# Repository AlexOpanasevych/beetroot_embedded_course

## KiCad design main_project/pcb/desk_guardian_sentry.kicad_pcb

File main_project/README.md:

# Main Project — Desk Guardian: Networked Sentry

A capstone that extends the **miniproject_module5** "Desk Guardian" PIR/buzzer/LED
board into a small networked environmental sentry: it still barks at motion, but
now also reads temperature/humidity/pressure, spins a PID-controlled cooling fan,
and serves a live status dashboard over Wi-Fi — no PC/serial monitor required to
see what it's doing.

Hardware is **Desk Guardian PCB rev B** (`pcb/`): the miniproject_module5 board
with the PIR/buzzer/LED circuitry unchanged, plus an on-board BME280 header and
a fan low-side driver for the new features — see [PCB — rev B](#pcb--rev-b).

## What it reuses, and from where

| Piece | Reused from | What changed |
|---|---|---|
| I2C driver style (`driver/i2c_master.h`) | module4.2 (SSD1306 ticker) | Same bus-init pattern, new device (BME280) instead of an OLED |
| BME280 register map + Bosch compensation math | module4.4 (STM32 BME280 telemetry) | Ported from STM32 HAL calls to ESP-IDF's `i2c_master_transmit`/`_transmit_receive` |
| Multi-producer -> single-consumer FreeRTOS queue | module6.3 | Two producers (BME280 poll task, PIR task) instead of three; one aggregator task owns all shared state |
| ISR + binary semaphore, 0% CPU while idle | module6.5 (emergency-stop task) | Applied to the PIR input instead of a panic button |
| PID fan controller (incl. the D-sign fix, anti-windup, and min-duty output normalization) | module5.6 | Same math, fed by BME280 temperature instead of a thermistor divider; PID step runs whenever a fresh reading arrives instead of on a fixed 50 ms timer |
| Wi-Fi STA connect (event group, auto-reconnect) | miniproject_module3 (Wi-Fi subwoofer amp) | Same connect logic, serving a status page instead of streaming audio |
| Buzzer/LED "bark" cadence | module1.3 (flash/gap blink constants) | Same 80 ms/60 ms flash/gap timing, applied to the buzzer+LED alert instead of a plain blink |
| PIR + buzzer + LED-eyes hardware | miniproject_module5 (Desk Guardian PCB) | Unchanged — same pins, same RC filtering |
| Fan driver circuit (Q2/D2/R11) | miniproject_module5's buzzer driver (Q1/D1/R6) | Same MMBT3904 + 1N4148 topology, switched to +5V, plus a base pull-down and bulk cap |

## Wiring

Carried over unchanged from miniproject_module5:

| Signal | ESP32-S3 pin | Notes |
|---|---|---|
| PIR_IN | IO4 | RC-filtered on the board, R5 already pulls it down when idle |
| Buzzer control | IO5 | via the board's existing NPN transistor driver |
| LED eye 1 | IO6 | |
| LED eye 2 | IO7 | |

New on rev B (were no-connect pins on rev A):

| Signal | ESP32-S3 pin | On-board | Notes |
|---|---|---|---|
| BME280 SDA | IO8 (U2 pad 12) | J3 pin 4, R9 4.7k pull-up, TP1 | |
| BME280 SCL | IO9 (U2 pad 17) | J3 pin 3, R10 4.7k pull-up, TP2 | |
| BME280 VIN / GND | 3V3 / GND | J3 pins 1 / 2, C6 100nF | GY-BME280 pin order (VIN GND SCL SDA); module's SDO tied to GND -> address 0x76 |
| Fan PWM | IO18 (U2 pad 11) | R11 1k -> Q2 base, TP3 | R12 10k holds the fan off while IO18 floats during boot |
| Fan | +5V / FAN_DRV | J4 pins 1 / 2, D2 flyback, C7 10uF, TP4 | 5V fan, **<= 150 mA** (MMBT3904 is rated 200 mA) |

## Architecture

```
                 ISR (rising edge)
   PIR (IO4) ────────────────────► motion semaphore ──► pir_task
                                                            │
                                                     bark (buzzer+LEDs,
                                                      module1.3 cadence)
                                                            │
                                                            ▼
   BME280 (I2C) ──► bme280_task ──────────────────►  sensor_hub queue
      (every 2s)                                    (module6.3 pattern)
                                                            │
                                                            ▼
                                                    aggregator_task
                                                  (single consumer,
                                                 owns system_state_t)
                                                     │           │
                                          fan_pid_on_new_        │
                                          temperature()          │
                                                     │           │
                                                     ▼           ▼
                                              LEDC fan PWM   sensor_hub_get_state()
                                               (IO18)              │
                                                                   ▼
                                                          web_dashboard (/, /status.json)
                                                             served over Wi-Fi STA
```

`aggregator_task` is the *only* reader of the shared queue and the only writer
of the sensor/motion fields of `system_state_t` — exactly the module6.3
invariant ("no shared mutable state between producers; the queue itself is the
synchronization"). The few status fields that don't come from sensors (fan
duty, Wi-Fi state, CPU load) are written by their owners through
`sensor_hub_set_*()`, under the same mutex. `pir_task` reacts to motion
immediately and independently of the queue (the buzzer/LEDs can't wait on a
consumer task), then reports the event into the same queue afterwards so the
dashboard picks it up too.

A fourth task, `cpu_monitor_task` (every 3s), measures CPU load and
critical-section timing — see the Performance sections below.

## Reliability

`aggregator_task`, `pir_task`, `bme280_task`, and `cpu_monitor_task` are each
registered with ESP-IDF's task watchdog (`esp_task_wdt_add`) and reset it
(`esp_task_wdt_reset`) at least every ~3s — including on `pir_task`'s idle
poll and inside its post-motion cooldown (which is a menuconfig value and,
together with the bark, already exceeds 5s at the default, so it sleeps in 1s
slices). A task that truly hangs (stuck I2C transaction, deadlocked mutex,
etc.) trips the 5s watchdog and reboots the board (`CONFIG_ESP_TASK_WDT_PANIC=y`)
instead of silently freezing the sentry, while legitimate quiet periods never
trip it.

## Performance — CPU load monitoring

`cpu_monitor.cpp` samples FreeRTOS run-time stats every 3s
(`configGENERATE_RUN_TIME_STATS`, `ulTaskGetIdleRunTimeCounter()`) and
computes load as a rolling window (delta between samples), not a
since-boot average, so it reflects current conditions rather than slowly
drifting as uptime grows. Logged every sample (`ESP_LOGW` once load reaches
the 70% budget, `ESP_LOGI` otherwise) and pushed to the dashboard's
`cpu_load_pct` field. Not yet measured on hardware; the busiest paths should
be the 2s BME280/PID cycle, dashboard requests, and Wi-Fi, so load is expected
to stay far below the 70% budget — the log will confirm or refute that.

## Performance — critical-section timing

`crit_timing.h/.cpp` is a small min/max/avg microsecond recorder
(`esp_timer_get_time()`-based) used to actually measure, not just assume,
how long this project's two real critical sections stay held:

- **`sensor_hub`'s state mutex** — every `sensor_hub_get_state()` /
  `_set_fan_duty()` / `_set_wifi()` / `_set_cpu_load()` call and
  `aggregator_task`'s own update time the span between a successful
  `xSemaphoreTake` and the matching `xSemaphoreGive` (wait-to-acquire time
  is deliberately excluded — that's contention, not hold time).
- **The PIR GPIO ISR** (`pir_isr_handler`) — timed end-to-end, since the
  whole handler body is the "critical section" there. `crit_timing_record()`
  is `IRAM_ATTR` (pure integer math) so it's safe to call from an ISR that's
  itself `IRAM_ATTR`.

The stats themselves are shared data too, so they're guarded: the mutex
stats are only touched while holding the state mutex, and the ISR stats sit
behind a `portMUX` spinlock shared by the ISR and the reporting task.

Both get logged (and their stats reset) every 3s alongside the CPU load
report, by `cpu_monitor.cpp`. Expect low-single-digit microseconds for the
mutex (it only ever guards a small struct copy/field write) and a similar
order of magnitude for the ISR (it just gives a semaphore) — if either
climbs into the hundreds of microseconds or higher, that's a real regression
worth investigating, not noise.

## PCB — rev B

KiCad 10 project in `pcb/desk_guardian_sentry.*`, derived from
miniproject_module5's `desk_guardian` board (the original there is left
untouched as the rev A submission).

- **Board:** 2-layer, 78 x 106 mm, ESP32-S3-WROOM-1 soldered directly
  (antenna overhanging the top edge), USB-C 5V in -> AMS1117-3.3 LDO.
- **Rev B additions** (lower-right area, previously empty): J3 BME280 header,
  R9/R10 I2C pull-ups, C6 decoupling; Q2/D2/R11/R12/C7 fan driver, J4 fan
  header; test points TP1 SDA, TP2 SCL, TP3 FAN_PWM, TP4 FAN_DRV, TP5 GND.
  Both headers sit on the right board edge for off-board cabling.
- **Power / filtering:** C6 100nF right at the BME280 header's 3V3/GND pins;
  C7 10uF bulk on +5V next to the fan header, to absorb motor current spikes
  locally instead of pulling them back through the whole +5V run. D2 clamps
  the fan's inductive kick when Q2 switches off.
- **Signal / power separation:** F.Cu is a solid GND pour, so the new routing
  stays on B.Cu wherever possible — 310 of 367 mm (84%); the F.Cu pieces are
  short pad escapes plus the 15 mm local FAN_BASE net between R11/R12/Q2.
  Power runs are wider (+5V / FAN_DRV 0.6 mm, +3V3 0.4 mm) than signals
  (0.25 mm). Fan current reaches J4 on its own 0.6 mm +5V branch from the
  USB input rather than through the LDO's traces (~11 mV drop at 150 mA).
- **High-speed considerations:** nothing on this board is fast — I2C runs at
  100 kHz and the fan PWM at 5 kHz, so trace length and impedance matching
  aren't critical. The one RF-sensitive part, the WROOM antenna, has no
  copper routed under or near it.
- **Verification:** ERC 0 errors; DRC 0 errors, 0 unconnected items, 0
  schematic-parity issues. The only warnings are ones rev A already had
  (library-version drift on a few symbols, U2's silkscreen clipped by the
  board edge because the antenna overhangs).

## Build & run

```
pio run -t menuconfig
# -> "Desk Guardian Sentry Configuration": set your Wi-Fi SSID/password,
#    the fan's PID setpoint temperature, and the motion cooldown.

pio run -e esp32-s3-devkitc-1
pio run -e esp32-s3-devkitc-1 -t upload
pio device monitor -b 115200   # watch for "Got IP: ..."
```

Then open `http://<that-ip>/` in a browser on the same LAN. The page polls
`/status.json` every 2 seconds; a motion event turns the "Motion" card red
until the next PIR cooldown window ends.

## Known limitations

- Wi-Fi is STA-only with no fallback: `wifi_sta_init()` waits up to 15s for
  the initial connection, then boots the rest of the system (PIR sentry,
  fan PID) regardless — the dashboard just stays unreachable until a
  connection succeeds in the background (watch the serial log for
  "No Wi-Fi after..." vs. "Got IP: ...").
- No wall-clock timestamps: `last_motion_ms`/`bme280_updated_ms` are
  milliseconds since boot (`xTaskGetTickCount()`), not real time — the board
  has no RTC and this project doesn't add SNTP, so treat them as relative
  ("Xs ago"), not absolute.
- The dashboard has no auth — anyone on the LAN can view it (and see when
  you're not at your desk). Fine for a demo, not for anything beyond a
  trusted home/lab network, same caveat as the subwoofer amp's UDP stream.
- PID coefficients are the module5.6 starting values, carried over as-is;
  the BME280's thermal mass/response in open air will differ from the
  thermistor-on-a-divider setup they were tuned for, so expect to retune
  Kp/Ki/Kd (watch the `SP/PV/OUT/PWM` log lines) once real hardware is wired up.

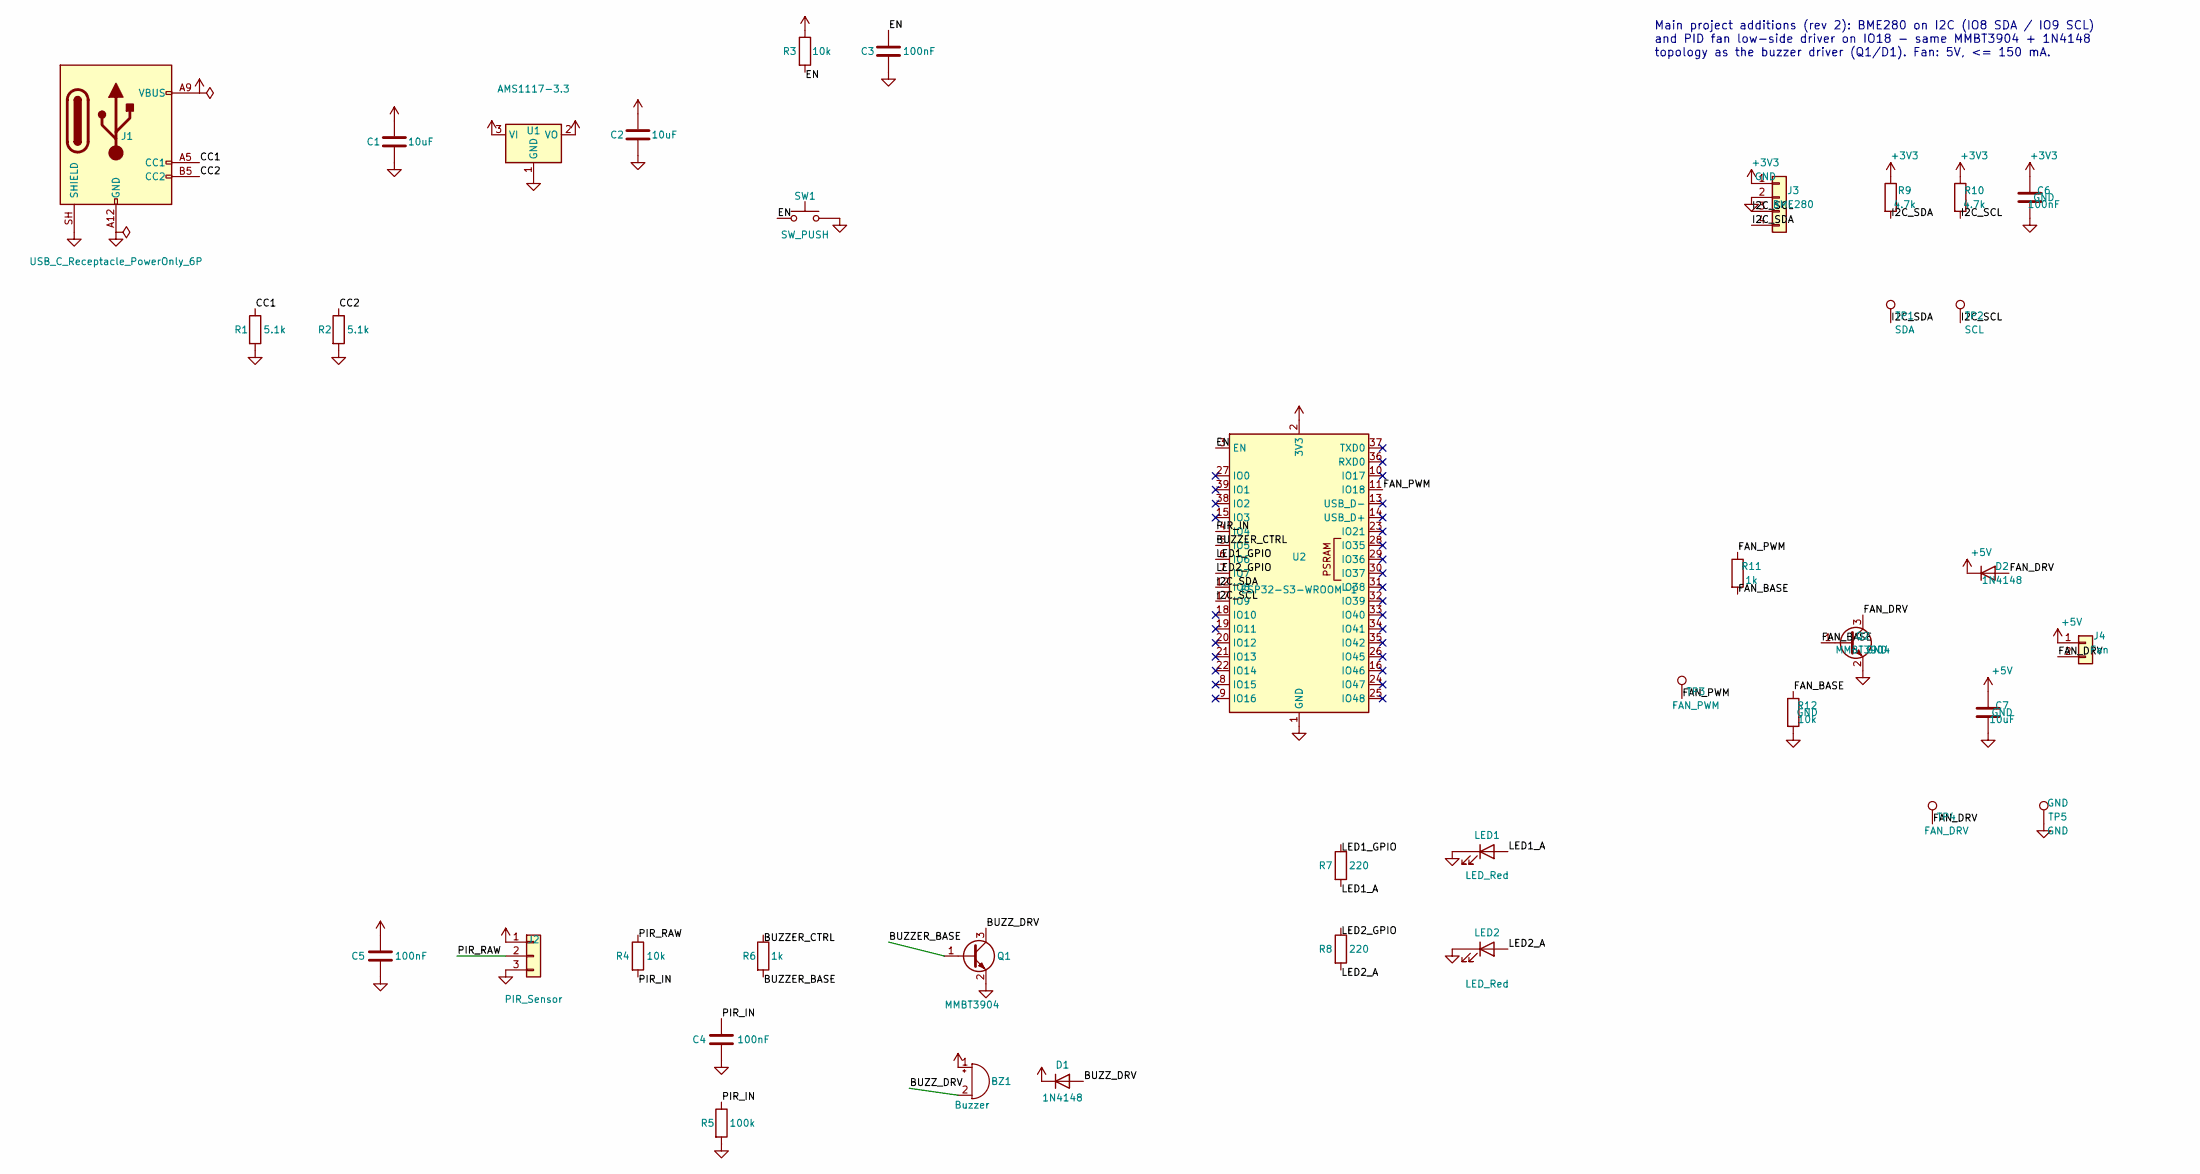
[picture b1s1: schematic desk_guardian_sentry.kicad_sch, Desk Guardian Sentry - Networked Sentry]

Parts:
BZ1: Buzzer; Buzzer_12x9.5RM7.6
C1, C2, C7: 10uF; C_0805_2012Metric
C3, C4, C5, C6: 100nF; C_0603_1608Metric
D1, D2: 1N4148; D_SOD-123
J1: USB_C_Receptacle_PowerOnly_6P; USB_C_Receptacle_GCT_USB4125-xx-x_6P_TopMnt_Horizontal
J2: PIR_Sensor; PinHeader_1x03_P2.54mm_Vertical
J3: BME280; PinHeader_1x04_P2.54mm_Vertical
J4: Fan; PinHeader_1x02_P2.54mm_Vertical
LED1, LED2: LED_Red; LED_0603_1608Metric
Q1, Q2: MMBT3904; SOT-23
R1, R2: 5.1k; R_0603_1608Metric
R3, R4, R12: 10k; R_0603_1608Metric
R5: 100k; R_0603_1608Metric
R6, R11: 1k; R_0603_1608Metric
R7, R8: 220; R_0603_1608Metric
R9, R10: 4.7k; R_0603_1608Metric
SW1: SW_PUSH; SW_SPST_B3U-1000P
TP1: SDA; TestPoint_Pad_D1.5mm
TP2: SCL; TestPoint_Pad_D1.5mm
TP3: FAN_PWM; TestPoint_Pad_D1.5mm
TP4: FAN_DRV; TestPoint_Pad_D1.5mm
TP5: GND; TestPoint_Pad_D1.5mm
U1: AMS1117-3.3; SOT-223-3_TabPin2
U2: ESP32-S3-WROOM-1

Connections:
+3V3: BZ1.1 (+), C2.1, C5.1, C6.1, D1.1 (K), J2.1, J3.1, R3.1, R9.1, R10.1, U1.2 (VO), U2.2 (3V3)
+5V: C1.1, C7.1, D2.1 (K), J1.A9 (VBUS), J1.B9 (VBUS), J4.1, U1.3 (VI)
/BUZZER_BASE: Q1.1 (B), R6.2
/BUZZER_CTRL: R6.1, U2.5 (IO5)
/BUZZ_DRV: BZ1.2 (-), D1.2 (A), Q1.3 (C)
/CC1: J1.A5 (CC1), R1.1
/CC2: J1.B5 (CC2), R2.1
/EN: C3.1, R3.2, SW1.1, U2.3 (EN)
/FAN_BASE: Q2.1 (B), R11.2, R12.1
/FAN_DRV: D2.2 (A), J4.2, Q2.3 (C), TP4.1
/FAN_PWM: R11.1, TP3.1, U2.11 (IO18)
/I2C_SCL: J3.3, R10.2, TP2.1, U2.17 (IO9)
/I2C_SDA: J3.4, R9.2, TP1.1, U2.12 (IO8)
/LED1_A: LED1.2 (A), R7.2
/LED1_GPIO: R7.1, U2.6 (IO6)
/LED2_A: LED2.2 (A), R8.2
/LED2_GPIO: R8.1, U2.7 (IO7)
/PIR_IN: C4.1, R4.2, R5.1, U2.4 (IO4)
/PIR_RAW: J2.2, R4.1
GND: C1.2, C2.2, C3.2, C4.2, C5.2, C6.2, C7.2, J1.A12 (GND), J1.B12 (GND), J1.SH (SHIELD), J2.3, J3.2, LED1.1 (K), LED2.1 (K), Q1.2 (E), Q2.2 (E), R1.2, R2.2, R5.2, R12.2, SW1.2, TP5.1, U1.1 (GND), U2.1 (GND), U2.40 (GND), U2.41 (GND)

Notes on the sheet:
Main project additions (rev 2): BME280 on I2C (IO8 SDA / IO9 SCL) and PID fan low-side driver on IO18 - same MMBT3904 + 1N4148 topology as the buzzer driver (Q1/D1). Fan: 5V, <= 150 mA.

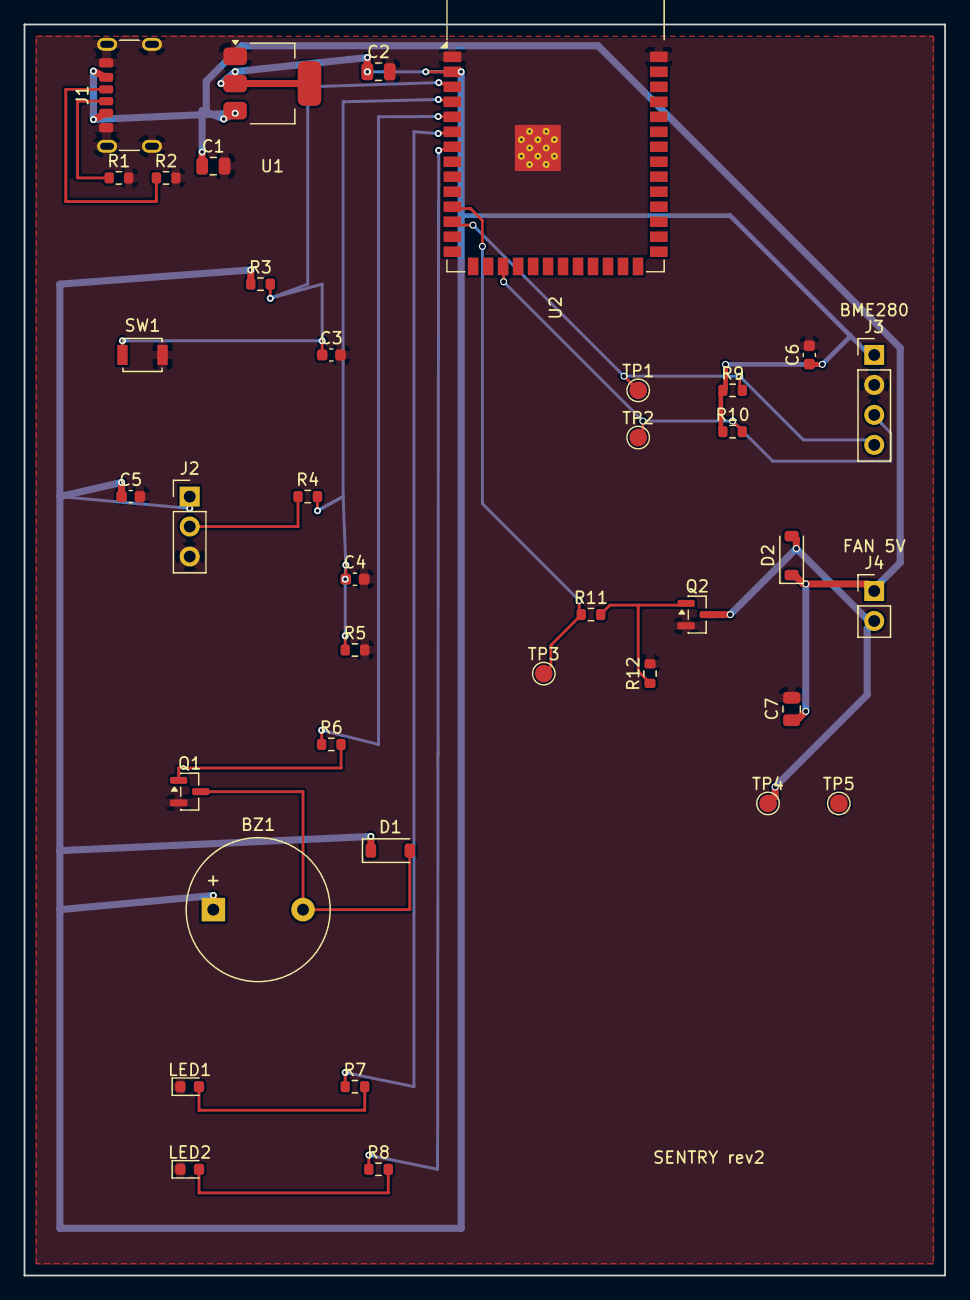
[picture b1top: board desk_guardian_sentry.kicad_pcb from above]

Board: 2 copper layers, 78.0 x 106.0 mm, 38 parts (0 on the bottom side), 20 nets.

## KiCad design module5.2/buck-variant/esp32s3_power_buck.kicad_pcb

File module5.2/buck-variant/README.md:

# Module 5.2 - ESP32-S3 Power Supply PCB Layout (Buck Converter Variant)

KiCad 10 project: the schematic from Module 5.1 (`buck-variant`), routed into a
2-layer PCB. This folder is a self-contained copy of the Module 5.1 project
(schematic + project files) plus the new, fully routed board
(`esp32s3_power_buck.kicad_pcb`), so it opens as one normal KiCad project.

The board was built programmatically with KiCad's bundled Python/`pcbnew`
(placing real library footprints, creating nets/tracks/vias from the
schematic's netlist, and adding the board outline), rather than by hand in
the PCB editor - this made it easy to derive exact pad coordinates from the
real footprint geometry and to verify placement/clearance numerically before
each DRC pass.

## Netlist source of truth

The board reproduces the schematic's netlist exactly (verified with
`--schematic-parity`, see DRC report below):

| Net | Pads |
|---|---|
| `/VIN` | J1.1, C1.1, U1.1 (VIN) |
| `/SW_NODE` | U1.2 (OUT), D1.1 (K), L1.1 |
| `+3V3` | L1.2, C2.1, U1.4 (FB), R1.2, U2.2 (3V3) |
| `/EN` | R1.1, C3.2, SW1.1, U2.3 (EN) |
| `GND` | C1.2, C2.2, C3.1, D1.2 (A), J1.2, SW1.2, U1.3 (GND+tab), U1.5 (ON/OFF), U2.1, U2.40, U2.41 |

Footprints used are exactly the ones assigned in the Module 5.1 schematic
(real KiCad library parts, no substitutions):

| Ref | Part | Footprint |
|---|---|---|
| J1 | Barrel jack | `Connector_BarrelJack:BarrelJack_CUI_PJ-063AH_Horizontal` |
| U1 | LM2596S-3.3 | `Package_TO_SOT_SMD:TO-263-5_TabPin3` |
| D1 | SS34 | `Diode_SMD:D_SMA` |
| L1 | 33uH inductor | `Inductor_SMD:L_10.4x10.4_H4.8` |
| C1 | 100uF/25V | `Capacitor_THT:CP_Radial_D6.3mm_P2.50mm` |
| C2 | 220uF/16V | `Capacitor_THT:CP_Radial_D6.3mm_P2.50mm` |
| C3 | 100nF | `Capacitor_SMD:C_0805_2012Metric` |
| R1 | 10k | `Resistor_SMD:R_0805_2012Metric` |
| SW1 | Push button | `Button_Switch_THT:SW_PUSH_6mm` |
| U2 | ESP32-S3-WROOM-1 | `RF_Module:ESP32-S3-WROOM-1` |

## Board outline

A rectangular `Edge.Cuts` outline, 90 mm x 80 mm, origin at (0,0). Size was
picked after placement: it gives the ESP32-S3 module's antenna keep-out zone
a clear margin to the board edge, keeps the buck-converter cluster's TO-263
tab and barrel jack clear of the board edge with a few mm to spare, and
leaves comfortable room for the reset network without needing to crowd
anything. It's larger than the absolute minimum a professional layout would
use, but that headroom is what made it possible to route entirely by hand
(via a script) without fighting for millimeters.

## Placement rationale

**ESP32-S3-WROOM-1 (U2)** is rotated so its antenna keep-out area (the wide
skirt at one end of the module's `F.CrtYd` courtyard - a rectangle roughly
21 mm x 48 mm, clearly larger than the module body itself) faces the board's
west edge, with the rest of the board's circuitry to the east and south of
the module body. This keeps the antenna area open (no other footprints'
courtyards or copper anywhere near it) and moves the noisy switching
regulator to the opposite side of the board from the RF module, which is
good practice for both antenna performance and switching noise coupling into
the 2.4 GHz front end.

**Buck converter switching loop (U1, D1, L1, C1, C2)** is clustered in the
board's north-east corner, physically as close together as the parts' real
footprint envelopes allow:
- `C1` (input bulk cap) sits right at U1's VIN pin.
- `D1` (catch diode) and `L1` (inductor) sit right at U1's OUT/switch-node
  pin - this is the loop that matters most for a buck converter (VIN through
  the FET, out through L1, with D1 providing the return path when the switch
  is off), so U1-D1-L1 form a tight triangle a few mm on a side rather than
  being spread across the board.
- `C2` (output bulk cap) sits just past L1's output pin.

The real footprint sizes (the TO-263 tab, the 10.4x10.4 mm shielded
inductor, the SMA diode) set a practical lower bound on how tight this loop
can be; given those envelopes, the loop here is about as small as it can be
made without overlapping courtyards.

**Reset network (R1, C3, SW1)** sits just south of the ESP32 module's EN/3V3/
GND pin row, i.e. as close as possible to the pins it serves. `SW1` (the
physical reset button) is placed toward the south-east of that group, away
from other components, so it stays reachable if the board is mounted for
production access to the button.

**Barrel jack (J1)** is mounted on the board's south edge (rotated 180 deg so
its plug-facing side lines up with the board edge), the standard placement
for a panel/edge-mount power connector so the DC plug is accessible from
outside an enclosure.

## Trace widths

- **Power/switching nets** (`/VIN`, `/SW_NODE`, `+3V3`, `GND`): **0.8 mm**.
  These carry the LM2596's several-amp switching current (and its return
  path on GND), so a wider trace than signal-level routing is used to keep
  resistive drop and heating low, per the requirement to use ~0.6-1.0 mm for
  power nets on a buck converter board.
- **`/EN`** (reset/enable logic signal): **0.3 mm**. This is a low-current
  logic-level net (10k pull-up, 100nF cap, push button), so a standard thin
  signal trace is appropriate; no need for the extra copper power traces use.
- **Vias**: 0.8 mm pad / 0.4 mm drill (standard-size vias), used to move GND
  (and two short `/VIN` hops, see below) between layers.

## Layer stackup / GND routing strategy

Standard 2-layer board (F.Cu / B.Cu). `/VIN`, `/SW_NODE`, `+3V3` and `/EN`
are routed entirely on the top layer (F.Cu). **GND is routed as a dedicated
tree entirely on the bottom layer (B.Cu)**, reached from each SMD GND pad by
a short top-layer stub into a via, and connected directly (no via needed) at
every through-hole GND pad (C1, C2, SW1, J1 are all THT, so their GND pads
already have copper on both layers).

This was a deliberate choice over a full copper pour/zone: with only 10
parts and 5 nets, a manually-routed GND tree is simple to verify net-by-net,
and putting GND on its own layer means the four F.Cu nets can be routed
without having to dodge a GND pour, and automatically can't short into each
other's layer. It also sidesteps any question of copper near the ESP32
module's antenna keep-out area - the GND tree on B.Cu was routed clear of
that whole rectangle, and no zone/pour was added there either. A full GND
copper pour (the "nice-to-have" in the brief) was consciously skipped in
favor of finishing a clean, fully-verified manual route; the existing B.Cu
GND tree could be turned into a pour later by just adding a `B.Cu` zone over
the board outline (minus the antenna keep-out) with the existing tracks left
in place as reinforcement.

Two short `/VIN` segments (about 2 mm each, near x=52.5, y=48-50) are
deliberately routed on B.Cu via a via-hop, purely to cross under the `+3V3`
trunk trace on F.Cu at one unavoidable intersection between the ESP32
module's south side and the buck cluster - everywhere else `/VIN` stays on
F.Cu.

## Deviations / notes on the clean DRC result

- **Minimum hole size relaxed to 0.2 mm.** The official KiCad
  `RF_Module:ESP32-S3-WROOM-1` footprint defines a cluster of small
  0.2 mm-drill plated pads under pin 41 (the antenna/thermal ground contact
  area) as part of its vendor-defined land pattern - this is baked into the
  real, verified footprint, not a routing choice made here. The board's
  minimum-hole design rule was lowered from KiCad's 0.3 mm default to 0.2 mm
  so DRC checks the real footprint instead of flagging it as an error. If
  this exact module/footprint is sent to fab, confirm the chosen
  manufacturer supports a 0.2 mm minimum drill (many do, sometimes at a
  higher price tier); this is a property of the ESP32-S3-WROOM-1 module's
  official footprint, not something introduced by this layout.
- U1's footprint (`TO-263-5_TabPin3`) exposes GND (pin 3) as two separate
  copper pads - the small gull-wing lead in the pin row, and the large
  thermal tab - both numbered "3" but not touching in copper. A short 0.8 mm
  F.Cu trace ties them together explicitly so the connection is real copper,
  not just a shared pad number.
- U2's pin 41 (GND) is exposed as a big 3.9x3.9 mm pad plus many small
  0.6x0.6 mm stitching pads, all physically overlapping the big pad - these
  are already one electrically continuous copper feature from the
  footprint itself, so only one via was placed on it.

## Final DRC report

Command used:
```
kicad-cli pcb drc esp32s3_power_buck.kicad_pcb --severity-all --exit-code-violations --schematic-parity
```

```
** Drc report for esp32s3_power_buck.kicad_pcb **
** Created on 2026-08-28T22:44:40 **
** Report includes: Errors, Warnings, Exclusions **

** Found 0 DRC violations **

** Found 0 unconnected pads **

** Found 0 Footprint errors **

** Ignored checks **
    - Footprint has no courtyard defined
    - Track endpoint not centered on via
    - Tuning profile track geometries
    - Footprint doesn't match symbol's footprint filters
    - Footprint component type doesn't match footprint pads

** End of Report **
```

0 errors, 0 warnings, 0 unconnected pads, 0 schematic-parity issues (every
net and every footprint on the board matches the Module 5.1 schematic
exactly).

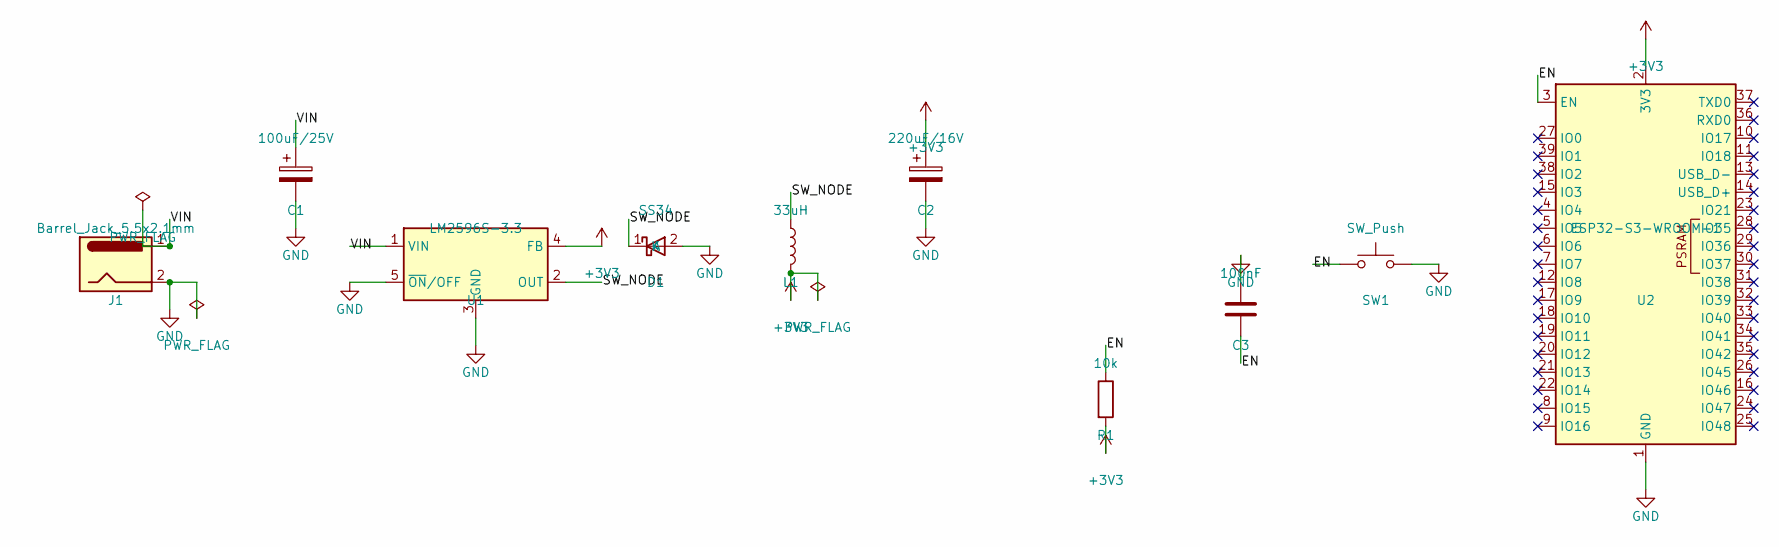
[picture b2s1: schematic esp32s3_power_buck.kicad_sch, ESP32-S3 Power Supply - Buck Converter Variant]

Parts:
C1: 100uF/25V; CP_Radial_D6.3mm_P2.50mm
C2: 220uF/16V; CP_Radial_D6.3mm_P2.50mm
C3: 100nF; C_0805_2012Metric
D1: SS34; D_SMA
J1: Barrel_Jack_5.5x2.1mm; BarrelJack_CUI_PJ-063AH_Horizontal
L1: 33uH; L_10.4x10.4_H4.8
R1: 10k; R_0805_2012Metric
SW1: SW_Push; SW_PUSH_6mm
U1: LM2596S-3.3; TO-263-5_TabPin3
U2: ESP32-S3-WROOM-1

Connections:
+3V3: C2.1, L1.2, R1.2, U1.4 (FB), U2.2 (3V3)
/EN: C3.2, R1.1, SW1.1, U2.3 (EN)
/SW_NODE: D1.1 (K), L1.1, U1.2 (OUT)
/VIN: C1.1, J1.1, U1.1 (VIN)
GND: C1.2, C2.2, C3.1, D1.2 (A), J1.2, SW1.2, U1.3 (GND), U1.5 (~ON/OFF), U2.1 (GND), U2.40 (GND), U2.41 (GND)

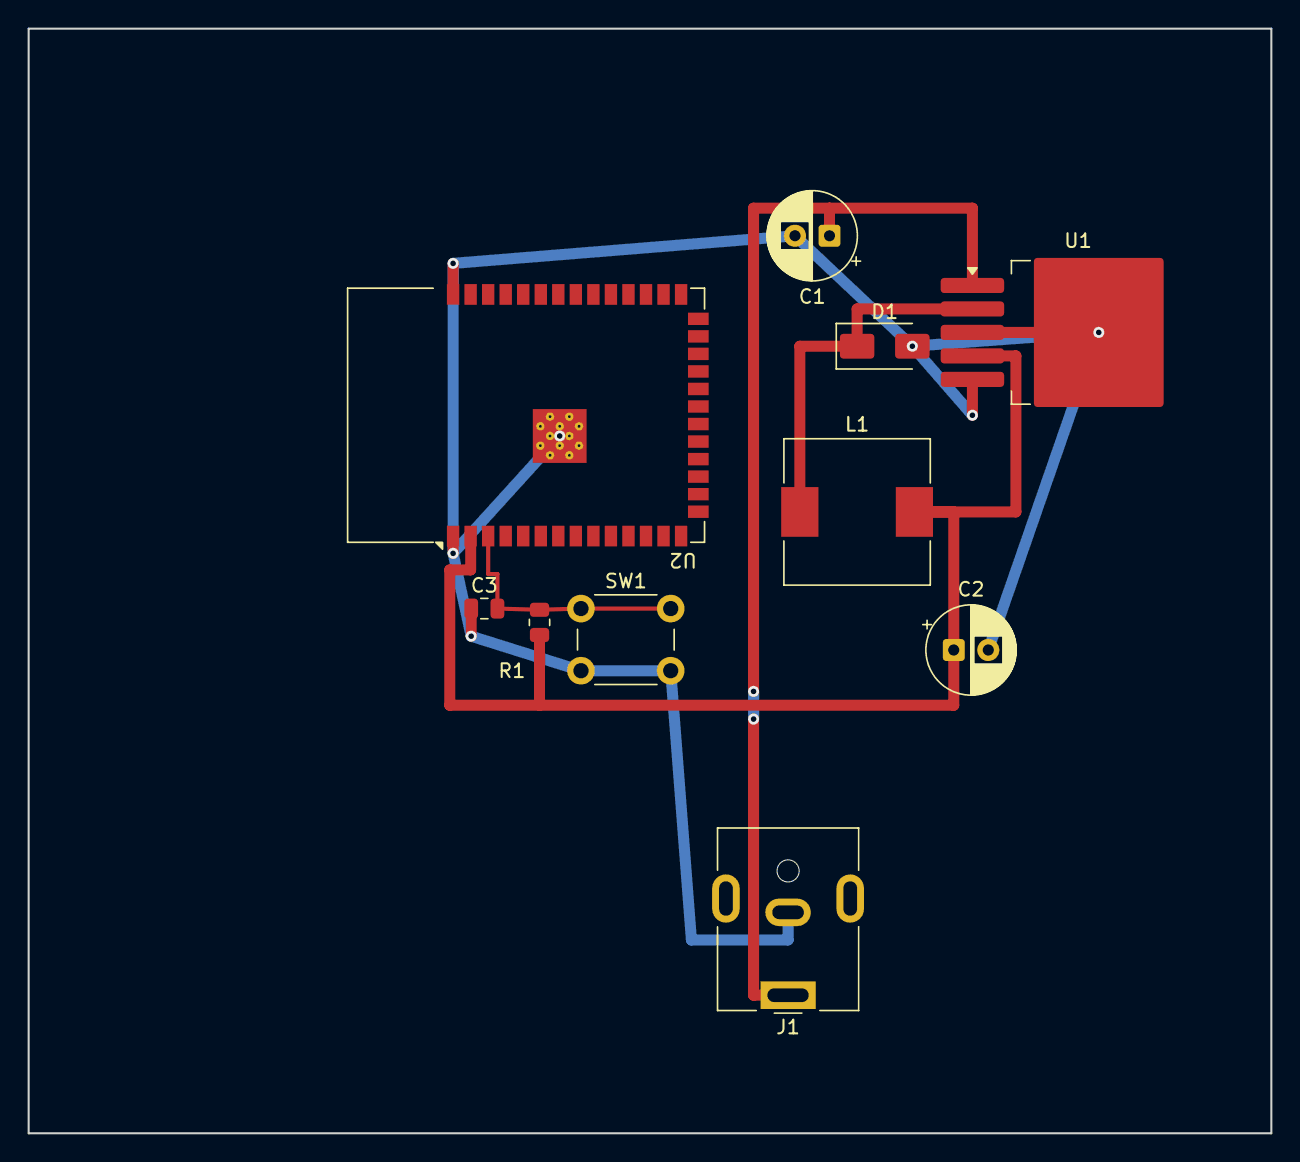
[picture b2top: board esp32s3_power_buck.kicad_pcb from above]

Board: 2 copper layers, 90.0 x 80.0 mm, 10 parts (0 on the bottom side), 5 nets.

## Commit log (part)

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2026-04-12 implemented module1.3, module1.4
2026-04-15 added module 1.5
2026-04-17 added module 1.6
2026-04-17 added single variable for analogReadMillivolts()
2026-04-18 added miniproject_module1
2026-05-06 implemented module 2.1
2026-05-18 implemented relay measurement, pwm throughpotentiometer + servo control
2026-05-29 implemented non-blocking led blinking using esp-idf framework
2026-05-29 implemented different button debounce methods. note that button is pull-up-pped and using rc-filter
2026-05-30 implemented exhaust fan timer using esp_timer periodic+one-shot callbacks
2026-05-30 added include folder
2026-06-01 implemented traffic light state machine with timeout-driven transitions
2026-06-03 implemented ADC potentiometer reading with calibration error table and real-time serial plotter
    - reads ADC1/CH9 (GPIO10) every 100ms using ESP-IDF v5 oneshot API with 12dB attenuation
    - prints config table on boot (resolution, attenuation, V_ref, calibration scheme)
    - computes U_manual via linear formula and U_cali via eFuse line-fitting calibration
    - outputs Error(%) between manual and calibrated voltage each sample
    - tools/serial_plotter.py: real-time matplotlib chart over serial, highlights non-linearity regions where error exceeds threshold
2026-06-03 add project scaffold, config files and example chart image
